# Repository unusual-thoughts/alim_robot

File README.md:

Réalisation de la carte d'alimentation
======================================

La carte d'alimentation est chargée de:
- Délivrer l'alimentation des différents composants du robot
- Informer de l'état de charge des batteries avec des leds
- Protéger les batteries

### Ancienne Carte

Un microcontrôleur Atmega328P utilisé pour évaluer la tension des batteries.

Les sources étaient trois batteries NiMh 12V de 2500mAh

Les régulateurs utilisés étaient DE-5W050 et DE-5WADJ

On peut utiliser des LM2596 a la place
Le plus simple serait de prendre des modules déja faits (très très peu chers)

### Budget Courant/tension

Elément            | U (V) | I (mA)             | P (W)
-------------------|-------|--------------------|------
Autres capteurs    | 3,3   | 5-50               | < .3
Raspberry          | 5     | 700 (1.5A max)     | < 7.5
Arduino/Teensy     | 5     | 10-20 (optimiste?) | ~.1
Capteurs           | 5     | 5-50               | < .5
Hokuyo             | 5     | 500 (800 init)     | < 4
Pont en H          | 5     | 5-10               | < .05
uArm               | 5     | < 5A               | < 25
Total 5V           | 5     | ~7A                | ~35
Servo Dynamixel    | 11.1  | 1.3A (x2)          | 28.86
Moteurs            | 24    | 800 (pic)          | < 38.4
Total (bat 1 et 2) | 24    | < 800              | < 38.4
Total (bat 3)      | 12    | < 5.42 A           | < 65

### Choix Régulateur(s)

Dynamixels non régulés? Ou step-down depuis le 24V? ou 12V?

Utilisation de [WEBENCH](http://webench.ti.com/) pour choix régulateur.

Régulateur                                            | Courant  | Package | Commentaires
------------------------------------------------------|----------|---------|----------------------------------------------
[Module LM2596](http://www.ebay.com/itm/321476590827) | << 3A    | Module  | Peu fiable (!)
[LM2596](http://www.ti.com/product/lm2596)            | max 3A   | ~TO263  | Pas assez de courant
[LM2678](http://www.ti.com/product/lm2678)            | max 5A   | ~TO263  | Fort encombrement, courant insuffisant, gros inducteur et diode
[TPS54821](http://www.ti.com/product/tps54821)        | max 8A   | QFN     | très performant, pas cher, très faible encombrement, compliqué à souder
[LMZ12008](http://www.ti.com/product/LMZ12008/)       | max 8A   | PFM     | très encombrant, très simple d'utilisation, extremement cher (15 euros)
[LMZ31710](http://www.ti.com/product/LMZ31710)        | max 10A  | QFN     | compromis, peu de composants externes, pas d'inducteur (!)

### Choix batterie 12V

On garde les 2 NiMh pour le 24V
LiPo pour le 12V:
[5800mAh](http://www.hobbyking.com/hobbyking/store/uh_viewItem.asp?idProduct=35957) ou [8000mAh](http://www.hobbyking.com/hobbyking/store/__38300__ZIPPY_Flightmax_8000mAh_3S1P_30C_Lipo_Pack_EU_Warehouse_.html)

### Schematic
#### Cicuit de protection batterie

#### Arduino

### Aperçu carte

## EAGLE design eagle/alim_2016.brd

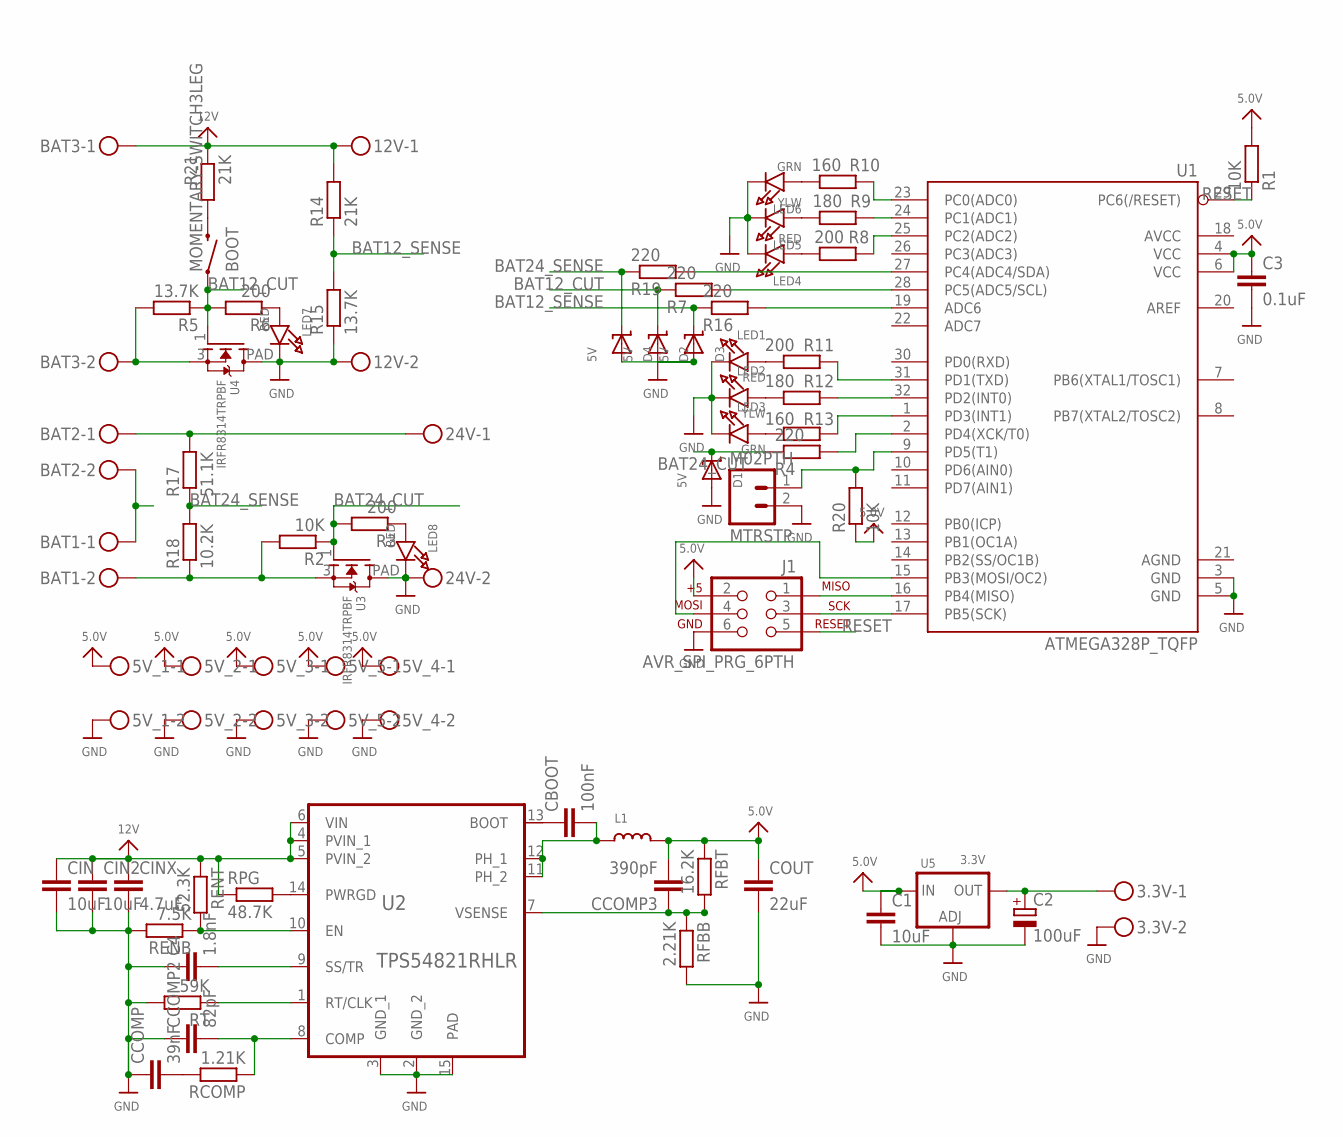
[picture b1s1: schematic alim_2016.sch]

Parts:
3.3V, 5V_1, 5V_2, 5V_3, 5V_4, 5V_5, 12V, 24V: WURTH_2PIN311; WURTH311
BAT1, BAT2, BAT3: WURTH_2PIN313; WURTH313_2
BOOT: MOMENTARY-SWITCH3LEG; 3LEGGED-TACT
C1: 10uF; C0805
C2: 100uF; E2,5-7
C3: 0.1uF; C0805
C4: 1.8nF; C0805
CBOOT: 100nF; C0805
CCOMP: 39nF; C0805
CCOMP2: 82pF; C0805
CCOMP3: 390pF; C0805
CIN, CIN2: 10uF; C0805
CINX: 4.7uF; C0805
COUT: 22uF; C0805
D1, D2, D3, D4: 5V; SOD-123
J1: AVR_SPI_PRG_6PTH; 2X3
L1: 2.2uH; XAL5030
LED1, LED4, LED7, LED8: RED; CHIPLED_0805_NOOUTLINE
LED2, LED5: YLW; CHIPLED_0805_NOOUTLINE
LED3, LED6: GRN; CHIPLED_0805_NOOUTLINE
MTRSTP: M02PTH; 1X02
R1, R2, R20: 10K; M0805
R3, R6, R8, R11: 200; M0805
R4, R7, R16, R19: 220; M0805
R5, R15: 13.7K; M0805
R9, R12: 180; M0805
R10, R13: 160; M0805
R14, R21: 21K; M0805
R17: 51.1K; M0805
R18: 10.2K; M0805
RCOMP: 1.21K; M0805
RENB: 7.5K; M0805
RENT: 52.3K; M0805
RFBB: 2.21K; M0805
RFBT: 16.2K; M0805
RPG: 48.7K; M0805
RT: 59K; M0805
U1: ATMEGA328P_TQFP; TQFP32-08
U2: TPS54821RHLR; S-PVQFN-N14
U3, U4: IRFR8314TRPBF; DPACK_1
U5: 3.3V; TO252

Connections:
5.0V: 5V_1.P$1, 5V_2.P$1, 5V_3.P$1, 5V_4.P$1, 5V_5.P$1, C1.1, C3.1, CCOMP3.2, COUT.1, J1.2, L1.2, R1.2, R20.1, RFBT.1, U1.4 (VCC), U1.6 (VCC), U5.2 (IN)
12V: 12V.P$1, BAT3.P$1, CIN.1, CIN2.1, CINX.1, R14.2, R21.1, RENT.1, RPG.1, U2.4 (PVIN_1), U2.5 (PVIN_2), U2.6 (VIN)
24V: 24V.P$1, BAT2.P$1, R17.2
BAT12_CUT: BOOT.1, D2.C, R5.1, R6.2, R7.1, U4.1 (G)
BAT12_SENSE: D3.C, R14.1, R15.2, R16.1
BAT24_CUT: D1.C, R2.1, R3.2, R4.1, U3.1 (G)
BAT24_SENSE: D4.C, R17.1, R18.2, R19.1
COMP: CCOMP2.2, RCOMP.1, U2.8 (COMP)
EN: RENB.1, RENT.2, U2.10 (EN)
GND: 3.3V.P$2, 5V_1.P$2, 5V_2.P$2, 5V_3.P$2, 5V_4.P$2, 5V_5.P$2, 12V.P$2, 24V.P$2, C1.2, C2.-, C3.2, C4.1, CCOMP.1, CCOMP2.1, CIN.2, CIN2.2, CINX.2, COUT.2, D1.A, D2.A, D3.A, D4.A, J1.6, LED1.C, LED2.C, LED3.C, LED4.C, LED5.C, LED6.C, LED7.C, LED8.C, MTRSTP.2, R15.1, RENB.2, RFBB.2, RT.2, U1.3 (GND), U1.5 (GND), U2.2 (GND_2), U2.3 (GND_1), U2.15 (PAD), U3.PAD (D), U4.PAD (D), U5.1 (ADJ)
MISO: J1.1, U1.16 (PB4(MISO))
MOSI: J1.4, U1.15 (PB3(MOSI/OC2))
unnamed: 3.3V.P$1, C2.+, U5.3 (OUT)
unnamed: R16.2, U1.19 (ADC6)
unnamed: BAT1.P$1, BAT2.P$2
unnamed: MTRSTP.1, R20.2, U1.9 (PD5(T1))
unnamed: BOOT.3 (2), R21.2
unnamed: BAT1.P$2, R2.2, R18.1, U3.3 (S)
unnamed: LED8.A, R3.1
unnamed: LED7.A, R6.1
unnamed: R4.2, U1.2 (PD4(XCK/T0))
unnamed: BAT3.P$2, R5.2, U4.3 (S)
unnamed: R9.2, U1.24 (PC1(ADC1))
unnamed: LED4.A, R8.1
unnamed: LED5.A, R9.1
unnamed: LED6.A, R10.1
unnamed: LED1.A, R11.1
unnamed: LED2.A, R12.1
unnamed: LED3.A, R13.1
unnamed: R8.2, U1.25 (PC2(ADC2))
unnamed: R10.2, U1.23 (PC0(ADC0))
unnamed: R7.2, U1.28 (PC5(ADC5/SCL))
unnamed: R13.2, U1.1 (PD3(INT1))
unnamed: R12.2, U1.32 (PD2(INT0))
unnamed: R11.2, U1.31 (PD1(TXD))
unnamed: R19.2, U1.27 (PC4(ADC4/SDA))
unnamed: CCOMP.2, RCOMP.2
unnamed: CBOOT.1, U2.13 (BOOT)
unnamed: RPG.2, U2.14 (PWRGD)
PH: CBOOT.2, L1.1, U2.11 (PH_2), U2.12 (PH_1)
RESET: J1.5, R1.1, U1.29 (PC6(/RESET))
RTCLK: RT.1, U2.1 (RT/CLK)
SCK: J1.3, U1.17 (PB5(SCK))
SSTR: C4.2, U2.9 (SS/TR)
VSENSE: CCOMP3.1, RFBB.1, RFBT.2, U2.7 (VSENSE)

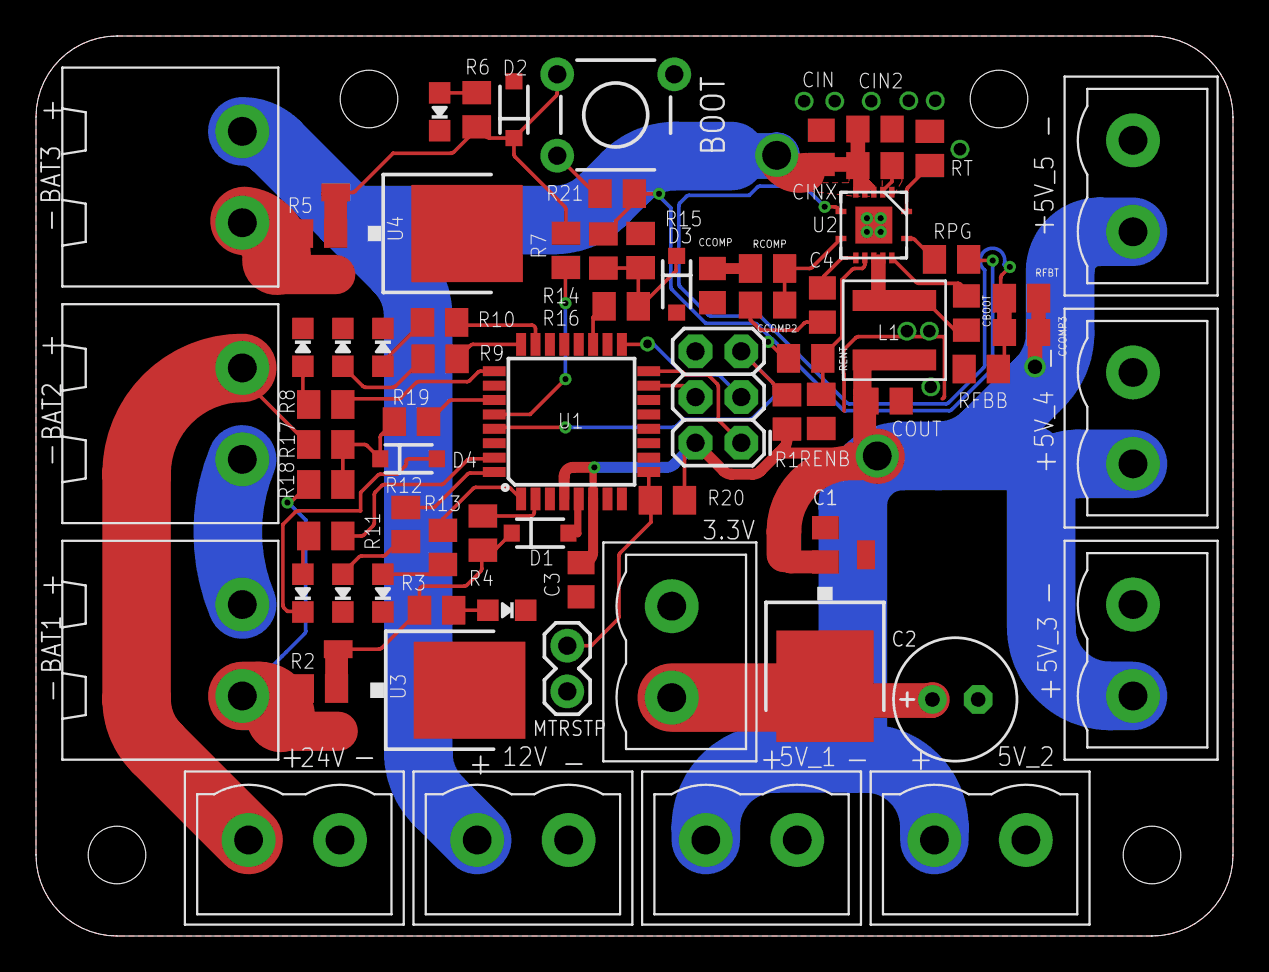
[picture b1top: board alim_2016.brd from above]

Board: 2 copper layers, 66.5 x 50.0 mm, 72 parts (0 on the bottom side), 45 nets.

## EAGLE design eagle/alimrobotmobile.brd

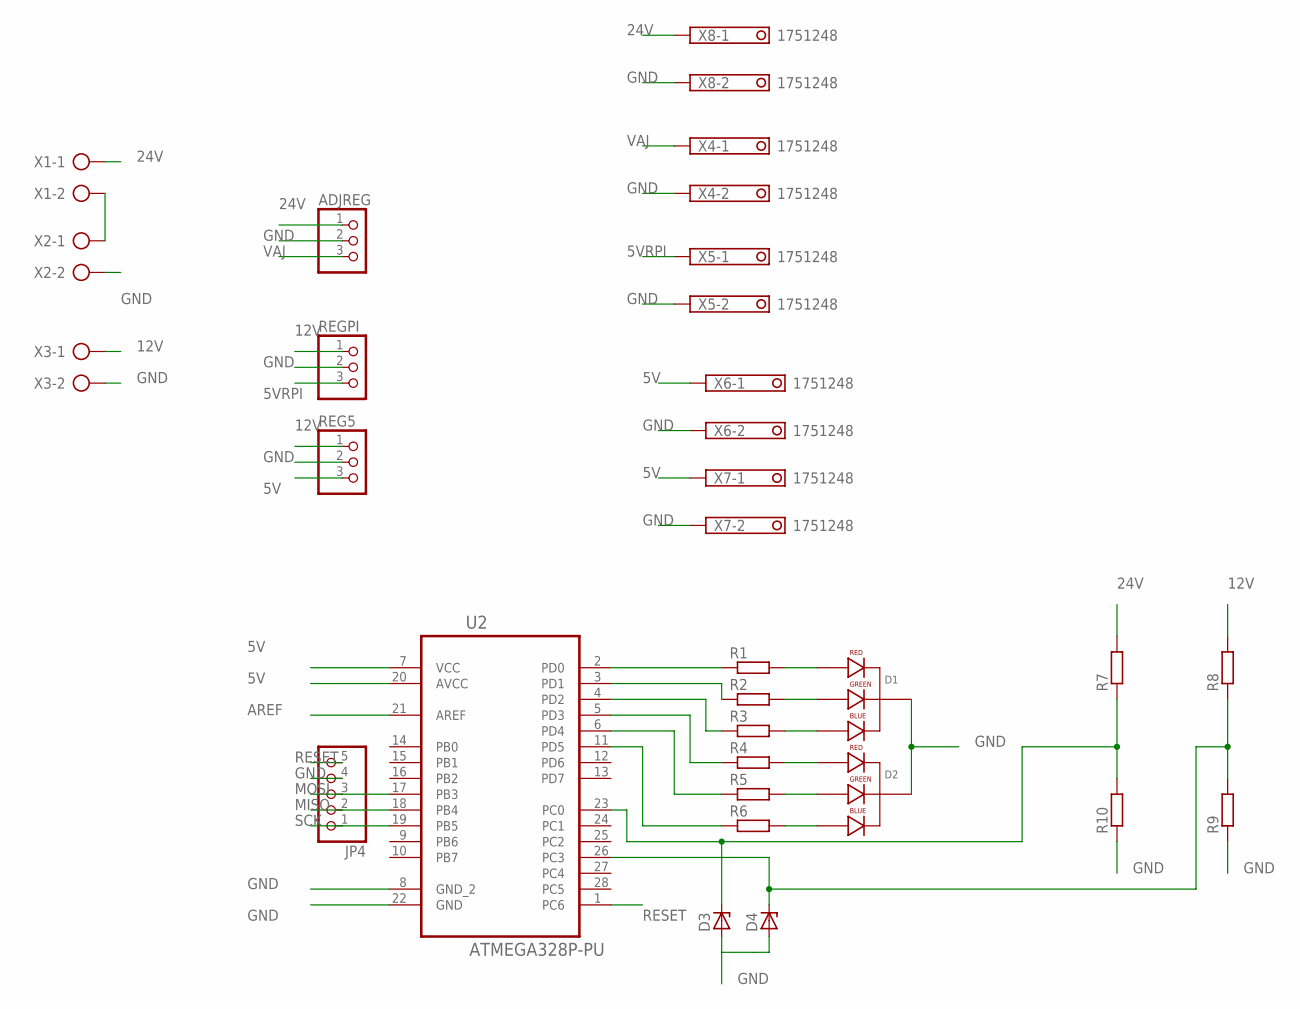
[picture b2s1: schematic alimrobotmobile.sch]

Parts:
ADJREG: PINHD-1X3; 1X03
D1, D2: LED-RGB-CC-THRUCLEAR; LED-RGB-THRU
D3, D4: ZENER-DIODEZD-12.5; ZDIO12.5
JP4: PINHD-1X5; 1X05
R1, R2, R3, R4, R5, R6, R7, R8, R9, R10: R-EU_0207/12; 0207/12
REG5: PINHD-1X3; 1X03
REGPI: PINHD-1X3; 1X03
U2: ATMEGA328P-PU; DIP254P762X457-28
X1, X2, X3: AK300/2
X4, X5, X6, X7, X8: 1751248

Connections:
5V: REG5.3, U2.7 (VCC), U2.20 (AVCC), X6.1, X7.1
5VRPI: REGPI.3, X5.1
12V: R8.2, REG5.1, REGPI.1, X3.1
24V: ADJREG.1, R7.2, X1.1, X8.1
AREF: U2.21 (AREF)
GND: ADJREG.2, D1.2 (CATHODE), D2.2 (CATHODE), D3.A, D4.A, JP4.4, R9.1, R10.1, REG5.2, REGPI.2, U2.8 (GND_2), U2.22 (GND), X2.2, X3.2, X4.2, X5.2, X6.2, X7.2, X8.2
MISO: JP4.2, U2.18 (PB4)
MOSI: JP4.3, U2.17 (PB3)
unnamed: R1.1, U2.2 (PD0)
unnamed: R2.1, U2.3 (PD1)
unnamed: D4.C, R8.1, R9.2, U2.26 (PC3)
unnamed: R3.1, U2.4 (PD2)
unnamed: R4.1, U2.5 (PD3)
unnamed: R5.1, U2.6 (PD4)
unnamed: R6.1, U2.11 (PD5)
unnamed: D1.1 (RED_CATHODE), R1.2
unnamed: D1.3 (GREEN_CATHODE), R2.2
unnamed: X1.2, X2.1
unnamed: D1.4 (BLUE_CATHODE), R3.2
unnamed: D2.1 (RED_CATHODE), R4.2
unnamed: D2.3 (GREEN_CATHODE), R5.2
unnamed: D2.4 (BLUE_CATHODE), R6.2
unnamed: D3.C, R7.1, R10.2, U2.23 (PC0)
RESET: JP4.5, U2.1 (PC6)
SCK: JP4.1, U2.19 (PB5)
VAJ: ADJREG.3, X4.1

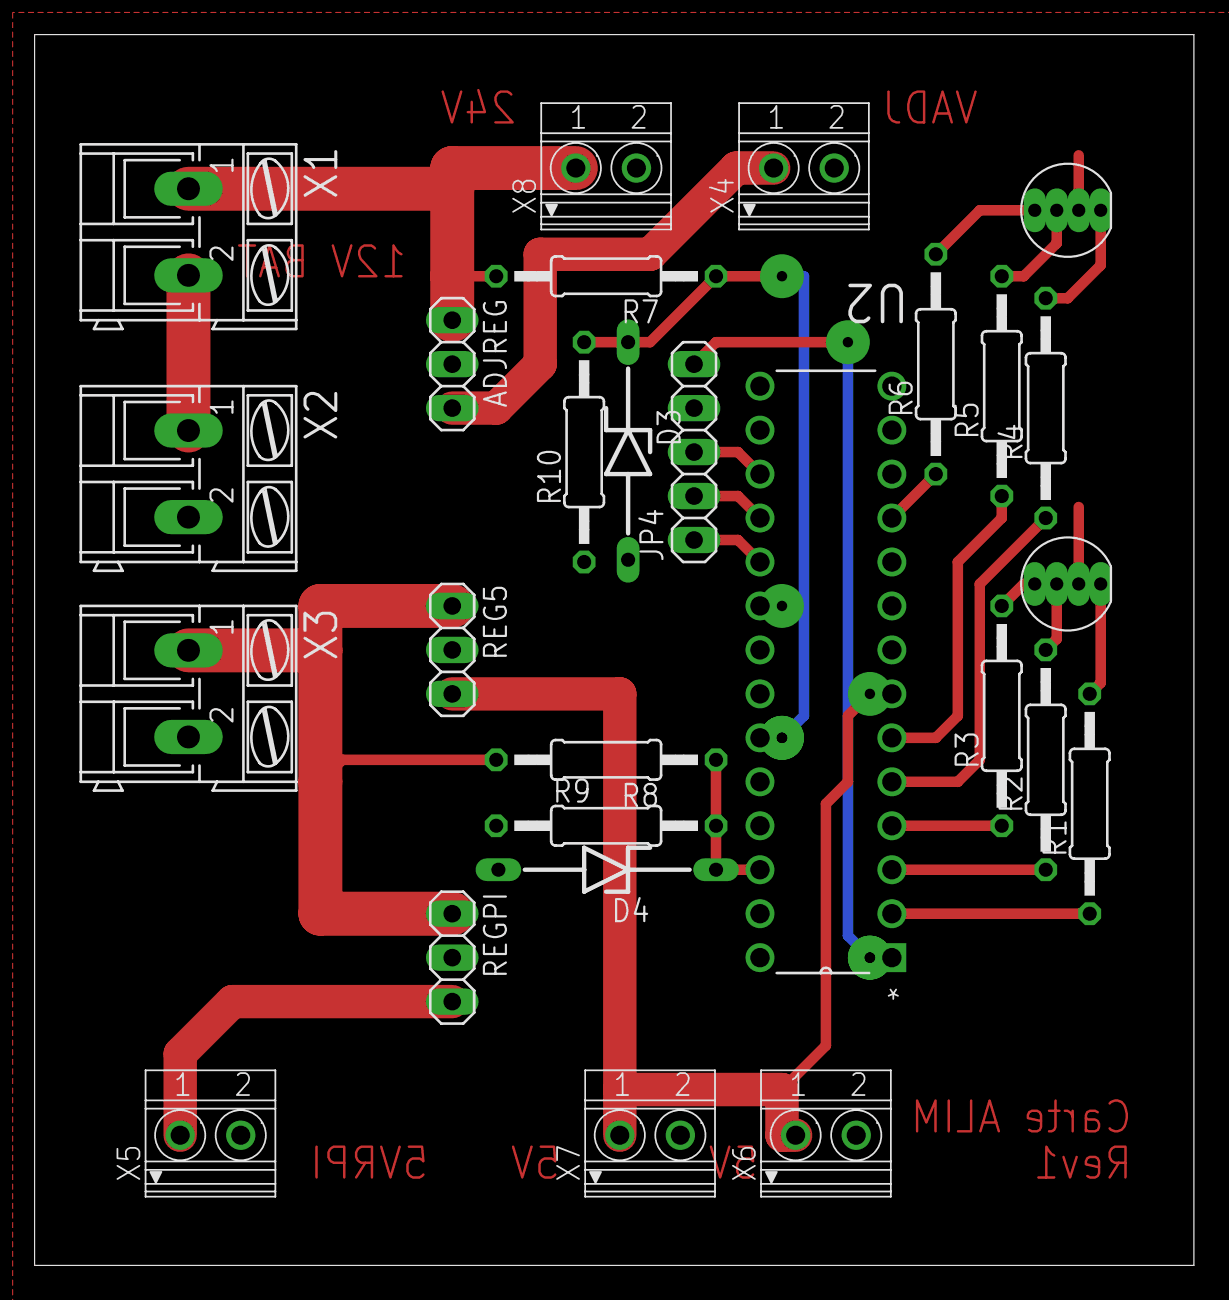
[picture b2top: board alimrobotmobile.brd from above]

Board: 2 copper layers, 67.0 x 71.1 mm, 27 parts (0 on the bottom side), 25 nets.

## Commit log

2015-11-19 add nicolas's files
2015-11-19 add doc
2015-11-26 Update current budget
2015-11-28 add custom library
2015-11-28 add first draft for new board
2015-11-28 thermal vias
2015-11-29 pcb rearranging
2015-11-29 remove extra switch, routing
2015-11-29 adding battery voltage sense
2015-11-29 adding other battery voltage sense
2015-11-29 clean up schematic
2015-11-30 clean up board
2015-12-01 most of the circuit finished
2015-12-01 neater
2015-12-01 more cleanup
2015-12-01 rearrange stuff
2015-12-01 Add uArm
2015-12-01 Update current draw
2015-12-03 add new switching regulator
2015-12-03 update readme, again
2015-12-03 add svg files
2015-12-03 resize svg
2015-12-03 add schematic preview
2015-12-03 resize tps svg
2015-12-04 add board preview
2015-12-07 route TPS chip
2015-12-17 cleanup
2015-12-23 changed connectors
2015-12-23 shuffle things around
2015-12-30 final version
2016-01-09 board sent to OSHPARK
2016-01-16 fix routing error: ADC7 cannot be a GPIO
2016-01-16 added arduino board config and test sketch
2016-01-16 increase via tenting
2016-01-16 fix qfn package

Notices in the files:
parts and their libraries:
microbuilder: This work is placed in the public domain, and may be freely used for commercial and non-commercial work with the following conditions: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
SparkFun-DigitalIC: Licensing: Creative Commons ShareAlike 4.0 International - https://creativecommons.org/licenses/by-sa/4.0
